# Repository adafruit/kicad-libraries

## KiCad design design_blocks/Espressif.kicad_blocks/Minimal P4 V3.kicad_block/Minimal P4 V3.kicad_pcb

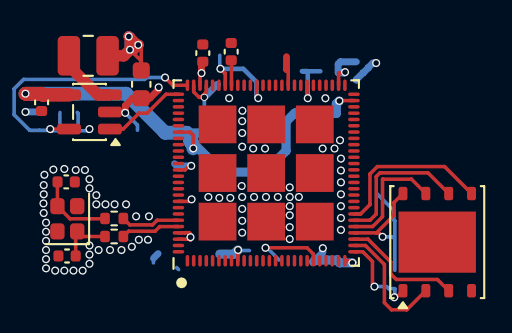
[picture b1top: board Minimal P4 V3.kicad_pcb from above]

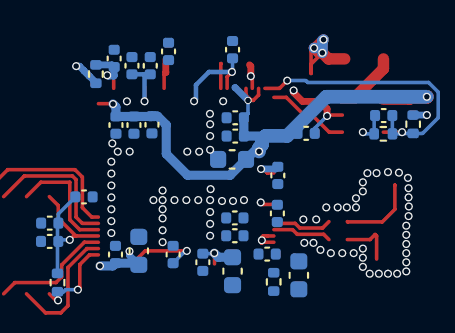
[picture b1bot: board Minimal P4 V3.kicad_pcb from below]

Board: 4 copper layers, 45 parts (32 on the bottom side), 21 nets.

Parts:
C1, C42: 4.7uF; C_0402_1005Metric
C2: 22pF; C_0402_1005Metric
C3: 22uF; C_0603_1608Metric
C4, C5: 12pF; C_0402_1005Metric
C6, C7, C8, C9, C12, C13, C15, C16, C21, C23, C24, C25, C26, C31, C32, C33, C40: 0.1uF; C_0402_1005Metric
C11, C14, C20, C28: 10uF; C_0603_1608Metric
C17, C18, C27, C29, C30: 1uF; C_0402_1005Metric
C41: 10nF; C_0402_1005Metric
L1: 2.2uH; L_1008_2520Metric
R1, R2: 499k; R_0402_1005Metric
R3, R4, R39: 0; R_0402_1005Metric
R28, R200: 10k; R_0402_1005Metric
U1: TLV62569DBV; SOT-23-5
U2: ESP32-P4
U3: W25Q128JVS; WSON-8-1EP_6x5mm_P1.27mm_EP3.4x4.3mm
Y1: 40MHz(+-10 ppm) C501798; Crystal_SMD_2016-4Pin_2.0x1.6mm

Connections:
+3.3V: C1.1, C6.1, C7.1, C9.1, C11.1, C12.1, C13.1, C14.1, C16.1, C20.1, C21.1, C23.1, C24.1, C40.1, C41.1, C42.1, R200.2, U1.4 (VIN), U2.9 (VDD_LP), U2.21 (VDD_IO_0), U2.51 (VDD_USBPHY), U2.62 (VDD_IO_4), U2.75 (VDD_LDO), U2.77 (VDD_DCDCC), U2.85 (VDD_IO_5), U2.96 (VDD_IO_6), U2.101 (VDD_ANA), U2.102 (VDD_BAT)
/Minimal P4 V3/EN_DCDC: U1.1 (EN), U2.79 (EN_DCDC)
/Minimal P4 V3/FB_DCDC: C2.2, R1.1, R2.2, U1.5 (FB), U2.78 (FB_DCDC)
/Minimal P4 V3/FLASH_CK: U2.32 (FLASH_CK), U3.6 (CLK)
/Minimal P4 V3/FLASH_CS: R28.1, U2.27 (FLASH_CS), U3.1 (~CS)
/Minimal P4 V3/FLASH_D: U2.33 (FLASH_D), U3.5 (DI/IO_{0})
/Minimal P4 V3/FLASH_HOLD: U2.31 (FLASH_HOLD), U3.7 (~HOLD/~RESET/IO_{3})
/Minimal P4 V3/FLASH_Q: U2.28 (FLASH_Q), U3.2 (DO/IO_{1})
/Minimal P4 V3/FLASH_WP: U2.29 (FLASH_WP), U3.3 (~WP/IO_{2})
/Minimal P4 V3/VDDO_FLASH: C17.1, U2.71 (VDDO_FLASH)
/Minimal P4 V3/VDDO_PSRAM: C18.1, C26.1, C27.1, U2.59 (VDD_PSRAM_0), U2.67 (VDD_PSRAM_1), U2.72 (VDDO_PSRAM)
/Minimal P4 V3/VDD_FLASH: C30.1, C31.1, C32.1, R28.2, U2.30 (VDD_FLASH_IO), U3.8 (VCC)
/Minimal P4 V3/VDD_HP: C2.1, C3.1, C8.1, C15.1, C28.1, C29.1, L1.2, R1.2, R39.1, U2.26 (VDD_HP_0), U2.76 (VDD_HP_2), U2.91 (VDD_HP_3)
/RESET: C33.1, R200.1, U2.103 (CHIP_PU)
GND: C1.2, C3.2, C4.1, C5.2, C6.2, C7.2, C8.2, C9.2, C11.2, C12.2, C13.2, C14.2, C15.2, C16.2, C17.2, C18.2, C20.2, C21.2, C23.2, C24.2, C25.2, C26.2, C27.2, C28.2, C29.2, C30.2, C31.2, C32.2, C33.2, C40.2, C41.2, C42.2, R2.1, U1.2 (GND), U2.105 (GND), U3.4 (GND), Y1.2 (G), Y1.4 (G)
unnamed: C4.2, R3.2, Y1.1
unnamed: C5.1, R4.2, Y1.3
unnamed: L1.1, U1.3 (SW)
unnamed: C25.1, R39.2, U2.54 (VDD_HP_1)
unnamed: R4.1, U2.99 (XTAL_N)
unnamed: R3.1, U2.100 (XTAL_P)

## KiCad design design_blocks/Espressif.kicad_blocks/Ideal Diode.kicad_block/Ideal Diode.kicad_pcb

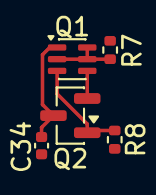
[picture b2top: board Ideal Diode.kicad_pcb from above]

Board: 4 copper layers, 5 parts (0 on the bottom side), 5 nets.

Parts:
C34: 1uF/16V(10%); C_0402_1005Metric
Q1: MBT3906DW1; SOT-363_SC-70-6
Q2: AO3401A; SOT-23
R7: 10K(1%); R_0402_1005Metric
R8: 51K(1%); R_0402_1005Metric

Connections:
/FS_VBUS: C34.1, Q1.1 (E1), Q2.3 (D)
GND: C34.2, R7.2, R8.2
unnamed: Q1.2 (B1), Q1.5 (B2), Q1.6 (C1), R7.1
unnamed: Q1.3 (C2), Q2.1 (G), R8.1
VBUS: Q1.4 (E2), Q2.2 (S)

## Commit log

2026-04-16 V10 update and add ESP32-P4 V3 symbol
2026-04-20 Add ideal diode design block
2026-04-23 P4 minimal design block
2026-04-27 Add reset RC to pcb layout
2026-04-27 Remove nested group
